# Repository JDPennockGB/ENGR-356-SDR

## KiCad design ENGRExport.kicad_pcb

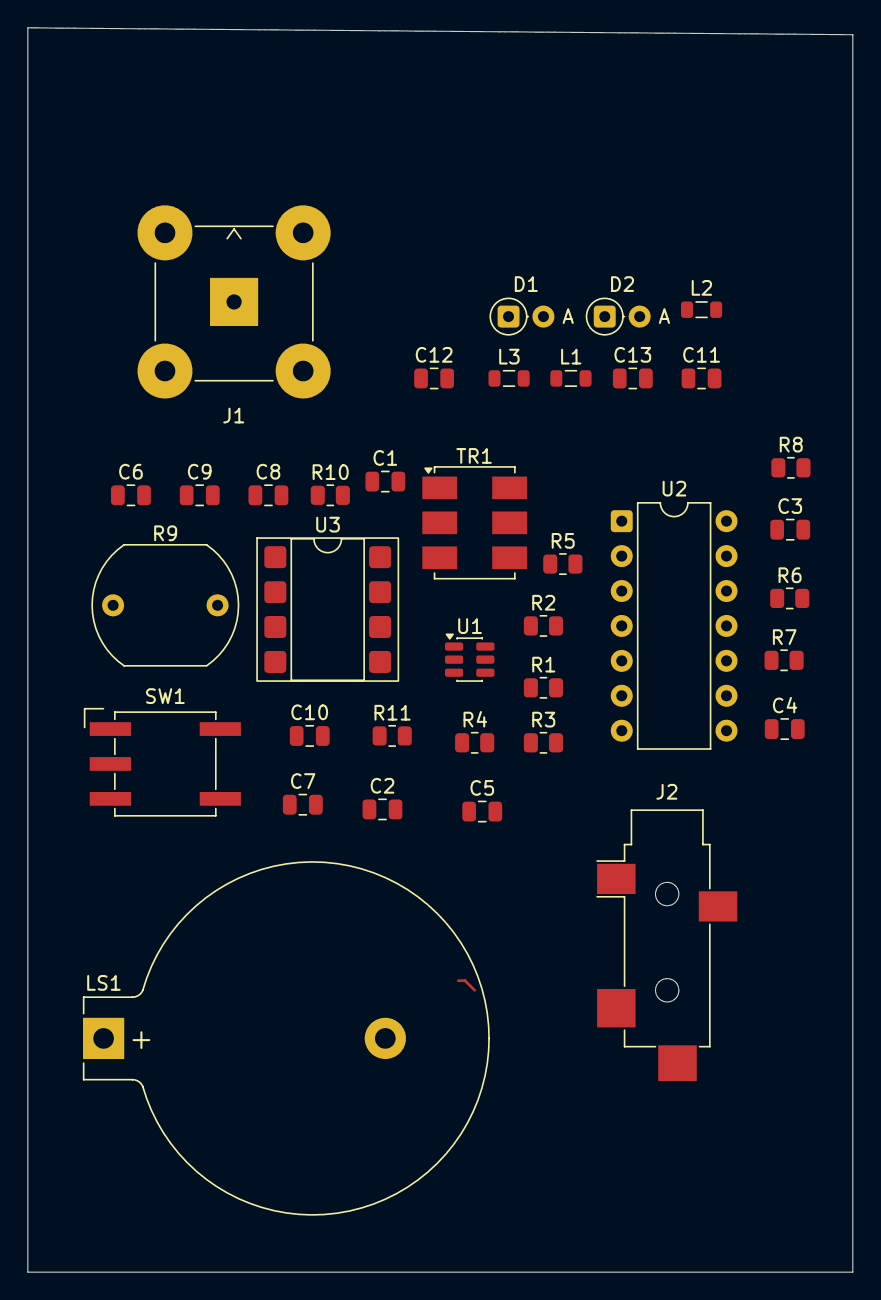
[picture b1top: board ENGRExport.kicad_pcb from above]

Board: 2 copper layers, 60.0 x 90.5 mm, 37 parts (0 on the bottom side), 30 nets.

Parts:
C1, C2, C5: 0.1uF; C_0805_2012Metric
C3, C4: 10nF; C_0805_2012Metric
C6, C9: 10uF; C_0805_2012Metric
C7, C10: 220uF; C_0805_2012Metric
C8: 0.05uF; C_0805_2012Metric
C11, C12: 174pF; C_0805_2012Metric
C13: 487pF; C_0805_2012Metric
D1, D2: 1N4148; D_DO-35_SOD27_P2.54mm_Vertical_AnodeUp
J1: Conn_Coaxial; BNC_TEConnectivity_1478035_Horizontal
J2: AudioJack3_Ground; Jack_3.5mm_CUI_SJ-3524-SMT_Horizontal
L1, L2, L3: 20uH; L_0805_2012Metric
LS1: Speaker; BatteryHolder_Keystone_104_1x23mm
R1, R2, R11: 10k; R_0805_2012Metric
R3: 100; R_0805_2012Metric
R4, R8: 1k; R_0805_2012Metric
R5: 47k; R_0805_2012Metric
R6, R7: 1.6k; R_0805_2012Metric
R9: 10k; R_LDR_10x8.5mm_P7.6mm_Vertical
R10: 10; R_0805_2012Metric
SW1: SW_Rotary_1x3_MP; Nidec_Copal_SH-7040B
TR1: ADT1-1WT; Mini-Circuits_CD542_H2.84mm
U1: 74LVC1G3157; SOT-23-6
U2: TL074; DIP-14_W7.62mm
U3: LM386; DIP-8_W7.62mm_SMDSocket_SmallPads

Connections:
+3.3V: C2.1, R2.1, U1.5 (VCC)
+5V: C5.1, U2.4 (V+), U3.6 (V+)
GND: C1.2, C2.2, C3.2, C5.2, C9.2, C11.2, C12.2, D2.1 (K), J1.2 (Ext), J2.TN, L2.2, L3.2, LS1.2, R1.2, R10.2, TR1.1, U1.2 (GND), U2.11 (V-), U3.2 (-), U3.4 (GND)
unnamed: C4.1, R6.1, R7.2
unnamed: C6.2, R9.2
unnamed: C7.1, SW1.1
unnamed: C7.2, LS1.1
unnamed: C8.1, SW1.4, U3.5
unnamed: C8.2, R10.1
unnamed: C10.1, SW1.3
unnamed: C10.2, R11.1
unnamed: C13.2, L1.1
unnamed: D1.2 (A), D2.2 (A)
unnamed: C11.1, C13.1, D1.1 (K), J1.1 (In), L2.1
unnamed: J2.R, J2.T
unnamed: J2.S, SW1.2
unnamed: R3.2, U1.6
unnamed: R4.2, U1.4
unnamed: R5.1, R6.2, U2.7
unnamed: TR1.4, U1.3
unnamed: TR1.6, U1.1
unnamed: C12.1, L1.2, L3.1, U2.3 (+)
unnamed: TR1.3, U2.1, U2.2 (-)
unnamed: C1.1, R1.1, R2.2, TR1.2, U2.5 (+)
unnamed: R4.1, R5.2, U2.6 (-)
unnamed: C3.1, R7.1, U2.10 (+)
unnamed: C4.2, U2.8, U2.9 (-), U2.12 (+)
unnamed: C6.1, R8.2, U2.13 (-), U2.14
unnamed: R9.1, U3.3 (+)
unnamed: C9.1, U3.7 (BYPASS)

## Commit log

2026-04-22 Create LTSpiceSimulations
2026-04-22 Create info-LTSpice with folder description
    Add description for LT Spice Simulations folder
2026-04-30 Add files via upload
    PCB design - Michael Roque
